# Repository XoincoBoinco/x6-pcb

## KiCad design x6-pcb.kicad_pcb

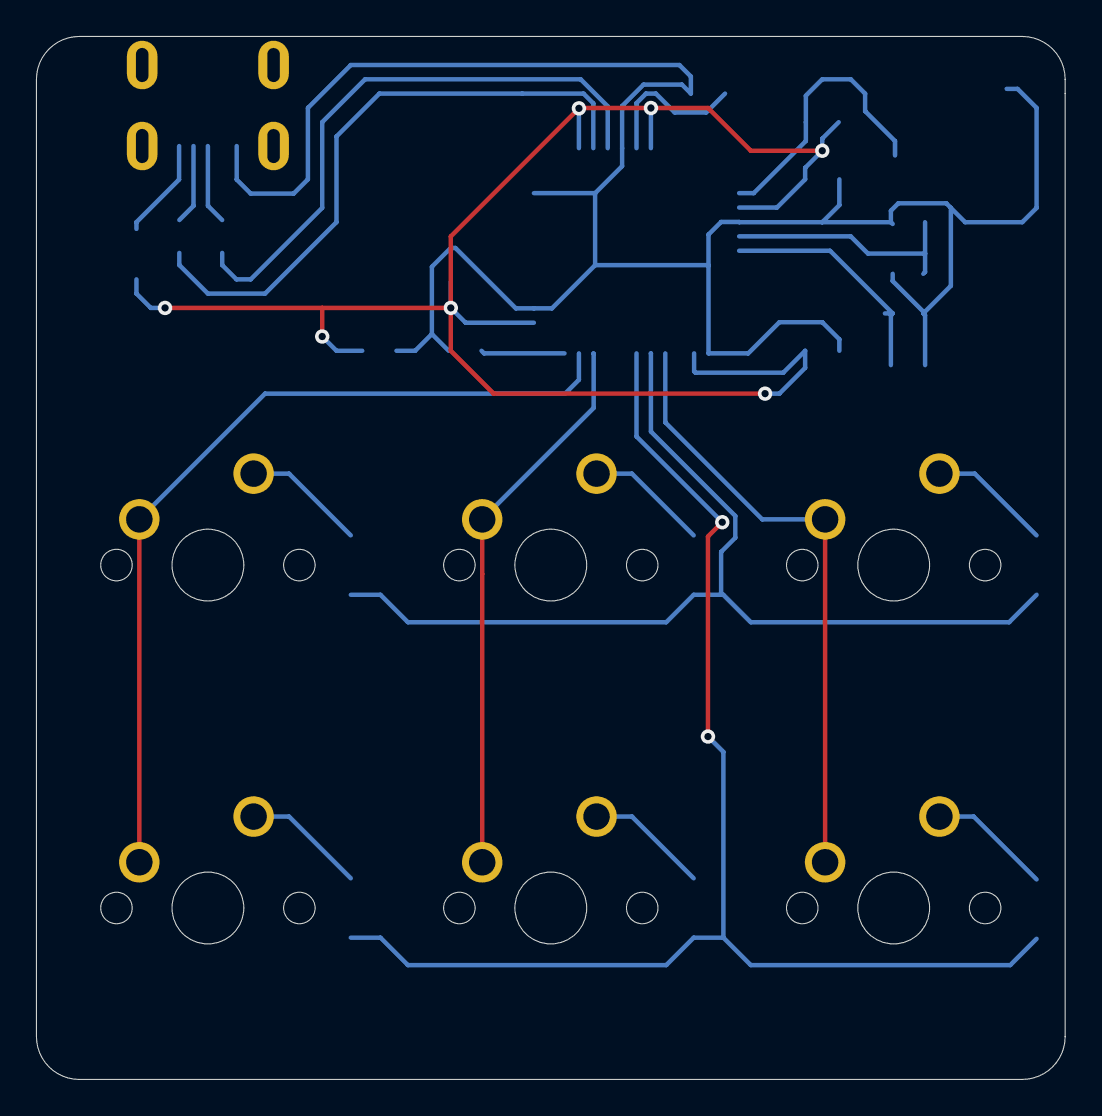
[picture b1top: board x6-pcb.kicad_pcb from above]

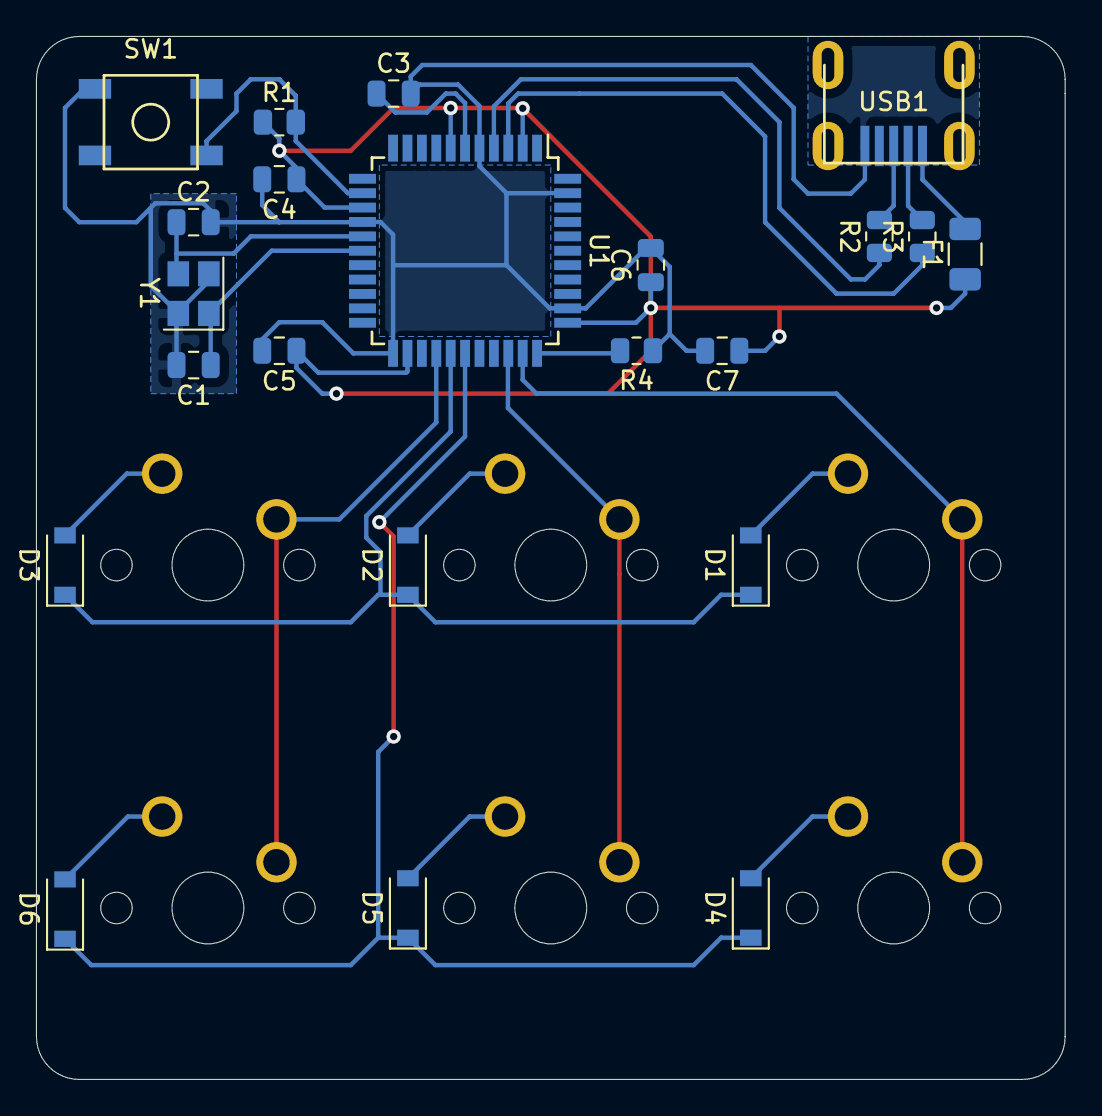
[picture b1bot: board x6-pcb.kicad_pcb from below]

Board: 2 copper layers, 57.2 x 57.9 mm, 28 parts (22 on the bottom side), 23 nets.

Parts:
C1, C2: 22pF; C_0805_2012Metric
C3: 1uF; C_0805_2012Metric
C4, C5, C6: 0.1uF; C_0805_2012Metric
C7: 10uF; C_0805_2012Metric
D1, D2, D3, D4, D5, D6: SOD-123; D_SOD-123
F1: 500mA; Fuse_1206_3216Metric
MX1, MX2, MX3, MX4, MX5, MX6: MX-NoLED; MXOnly-1U-NoLED
R1, R4: 10k; R_0805_2012Metric
R2, R3: 22; R_0805_2012Metric
SW1: SW_Push; SKQG-1155865
U1: ATmega32U4-AU; TQFP-44_10x10mm_P0.8mm
USB1: Molex-0548190589
Y1: 16MHz; Crystal_SMD_3225-4Pin_3.2x2.5mm

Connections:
+5V: C4.1, C5.1, C6.1, C7.1, F1.1, R1.1, U1.2, U1.7, U1.14, U1.24, U1.34, U1.44
COL0: MX1.1, MX4.1, U1.32
COL1: MX2.1, MX5.1, U1.31
COL2: MX3.1, MX6.1, U1.26
D+: R2.2, USB1.3
D-: R3.2, USB1.4
GND: C1.2, C2.2, C3.2, C4.2, C5.2, C6.2, C7.2, R4.1, SW1.1, U1.5, U1.15, U1.23, U1.35, U1.43, USB1.1, Y1.2, Y1.4
unnamed: C1.1, U1.17, Y1.1
unnamed: C2.1, U1.16, Y1.3
unnamed: C3.1, U1.6
unnamed: D1.2, MX1.2
unnamed: D2.2, MX2.2
unnamed: D3.2, MX3.2
unnamed: D4.2, MX4.2
unnamed: D5.2, MX5.2
unnamed: D6.2, MX6.2
unnamed: R1.2, SW1.2, U1.13
unnamed: R2.1, U1.4
unnamed: R3.1, U1.3
unnamed: R4.2, U1.33
ROW0: D1.1, D2.1, D3.1, U1.27
ROW1: D4.1, D5.1, D6.1, U1.28
VCC: F1.2, USB1.5

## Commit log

2020-11-18 Initialize project
2020-11-18 Add submodules
2020-11-18 Add footprint libraries
2020-11-18 Add pcb schematic
2020-11-18 Add pcb routing
2020-11-19 Removed switch LEDs
